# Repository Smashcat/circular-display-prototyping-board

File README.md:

# 1.28" Circular display prototyping board

This is a small prototyping PCB designed for the East Rising ER-TFT1.28-2 240x240 TFT display module with 24 pin connector.

The small connector is too small to hand solder, so this must be reflowed, but as there is only one part on the PCB a heatgun or iron could be used for this.

All the pins have been broken out to separate header pins, so that the same board can be used for other displays using the same connector, in case the pinouts are different!

I've included all the tech docs I have here too.

3D render and CAD download [here](https://a360.co/3l4JOM3)

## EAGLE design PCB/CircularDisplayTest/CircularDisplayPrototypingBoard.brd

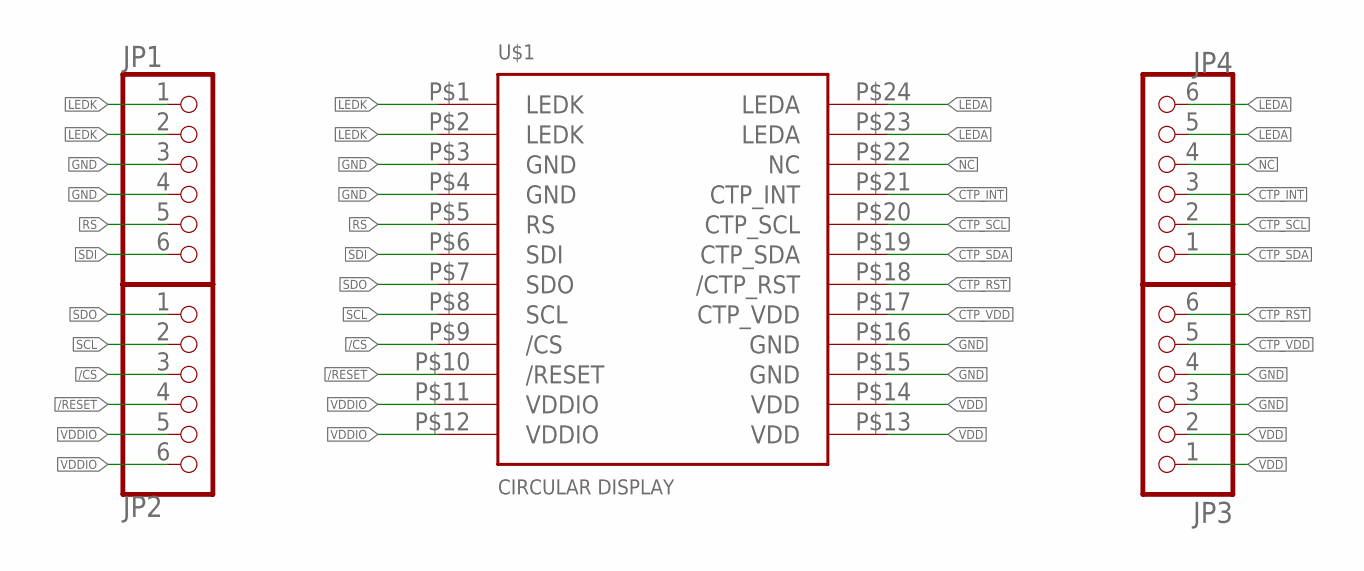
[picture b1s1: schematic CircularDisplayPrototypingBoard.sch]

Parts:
JP1, JP2, JP3, JP4: PINHD-1X6; 1X06
U$1: CIRCULAR-DISPLAY-1

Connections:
/CS: JP2.3, U$1.P$9 (/CS)
/RESET: JP2.4, U$1.P$10 (/RESET)
CTP_INT: JP4.3, U$1.P$21 (CTP_INT)
CTP_RST: JP3.6, U$1.P$18 (/CTP_RST)
CTP_SCL: JP4.2, U$1.P$20 (CTP_SCL)
CTP_SDA: JP4.1, U$1.P$19 (CTP_SDA)
CTP_VDD: JP3.5, U$1.P$17 (CTP_VDD)
GND: JP1.3, JP1.4, JP3.3, JP3.4, U$1.P$3 (GND), U$1.P$4 (GND), U$1.P$15 (GND), U$1.P$16 (GND)
LEDA: JP4.5, JP4.6, U$1.P$23 (LEDA), U$1.P$24 (LEDA)
LEDK: JP1.1, JP1.2, U$1.P$1 (LEDK), U$1.P$2 (LEDK)
NC: JP4.4, U$1.P$22 (NC)
RS: JP1.5, U$1.P$5 (RS)
SCL: JP2.2, U$1.P$8 (SCL)
SDI: JP1.6, U$1.P$6 (SDI)
SDO: JP2.1, U$1.P$7 (SDO)
VDD: JP3.1, JP3.2, U$1.P$13 (VDD), U$1.P$14 (VDD)
VDDIO: JP2.5, JP2.6, U$1.P$11 (VDDIO), U$1.P$12 (VDDIO)

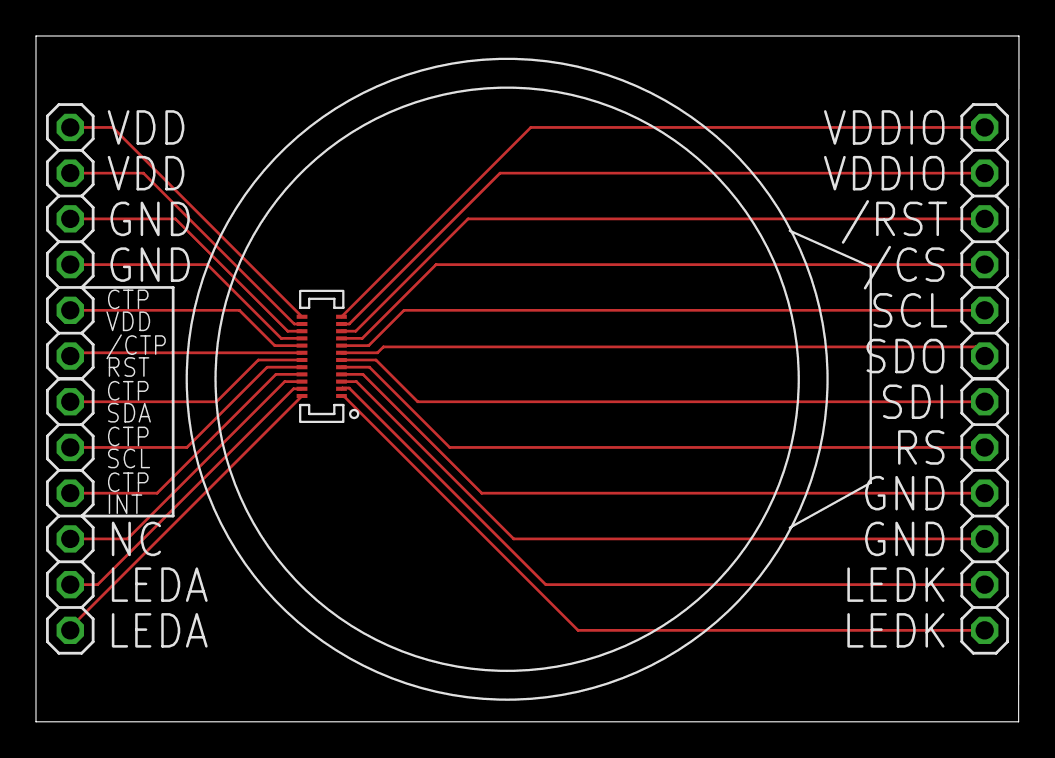
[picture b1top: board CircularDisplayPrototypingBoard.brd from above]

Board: 2 copper layers, 54.6 x 38.1 mm, 5 parts (0 on the bottom side), 17 nets.

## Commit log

2020-09-27 Updated render
2020-10-07 Added initial alpha version of Arduino library
2020-10-07 Cleaned up old images
2020-10-08 Renamed firmware to Arduino, as it now contains only the Arduino lib and examples
2020-10-11 Added new example with scaling
2020-12-09 Added stand-alone touchscreen test code
